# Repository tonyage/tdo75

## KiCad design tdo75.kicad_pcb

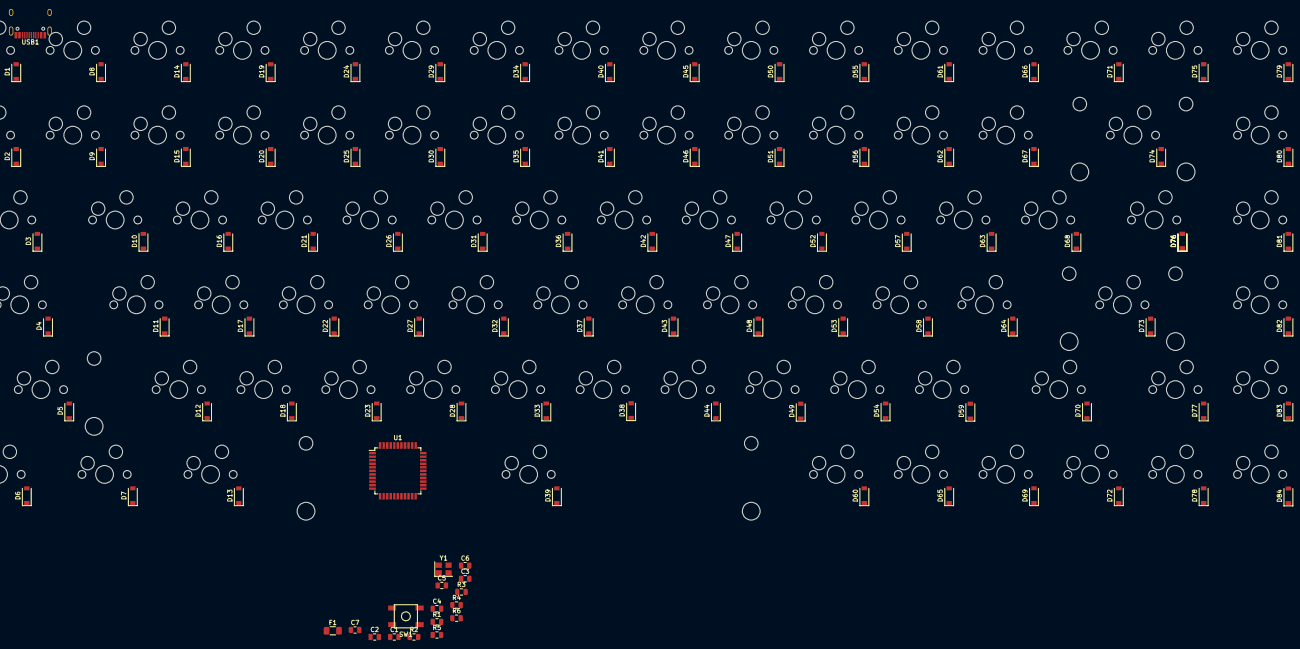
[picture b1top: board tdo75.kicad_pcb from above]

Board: 2 copper layers, 187 parts (0 on the bottom side), 120 nets, no tracks yet.

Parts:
C1, C3, C4: 0.1uF; C_0805_2012Metric
C2: 1uF; C_0805_2012Metric
C5, C6: 22pF; C_0805_2012Metric
C7: 10uF; C_0805_2012Metric
D1, D2, D3, D4, D5, D6, D7, D8, D9, D10, D11, D12, D13, D14, D15, D16, D17, D18, D19, D20, D21, D22, D23, D24, D25, D26, D27, D28, D29, D30, D31, D32, D33, D34, D35, D36, D37, D38, D39, D40, D41, D42, D43, D44, D45, D46, D47, D48, D49, D50, D51, D52, D53, D54, D55, D56, D57, D58, D59, D60, D61, D62, D63, D64, D65, D66, D67, D68, D69, D70, D71, D72, D73, D74, D75, D76, D76#2, D77, D78, D79, D80, D81, D82, D83, D84: D_Small; D_SOD-123
F1: 500mA; Fuse_1206_3216Metric
MX1, MX2, MX8, MX9, MX10, MX11, MX12, MX14, MX15, MX16, MX17, MX18, MX19, MX20, MX21, MX22, MX23, MX24, MX25, MX26, MX27, MX28, MX29, MX30, MX31, MX32, MX33, MX34, MX35, MX36, MX37, MX38, MX40, MX41, MX42, MX43, MX44, MX45, MX46, MX47, MX48, MX49, MX50, MX51, MX52, MX53, MX54, MX55, MX56, MX57, MX58, MX59, MX60, MX61, MX62, MX63, MX64, MX65, MX66, MX67, MX68, MX69, MX71, MX72, MX75, MX77, MX78, MX79, MX80, MX81, MX82, MX83, MX84: MX-NoLED; MXOnly-1U-Hotswap
MX3, MX76: MX-NoLED; MXOnly-1.5U-Hotswap
MX4, MX70: MX-NoLED; MXOnly-1.75U-Hotswap
MX5, MX73: MX-NoLED; MXOnly-2.25U-Hotswap
MX6, MX7, MX13: MX-NoLED; MXOnly-1.25U-Hotswap
MX39: MX-NoLED; MXOnly-6.25U-Hotswap
MX74: MX-NoLED; MXOnly-2U-Hotswap
R1, R2: 5.1k; R_0805_2012Metric
R3, R4: 22; R_0805_2012Metric
R5, R6: 10k; R_0805_2012Metric
SW1: SW_Push; SKQG-1155865
U1: ATmega32U4-AU; TQFP-44_10x10mm_P0.8mm
USB1: HRO-TYPE-C-31-M-12
Y1: 16MHz; Crystal_SMD_3225-4Pin_3.2x2.5mm

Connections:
+5V: C1.1, C3.1, C4.1, C7.1, F1.1, R5.2, U1.2, U1.7, U1.14, U1.24, U1.34, U1.44
COL0: MX1.1, MX2.1, MX3.1, MX4.1, MX5.1, MX6.1, U1.8
COL1: MX7.1, MX8.1, MX9.1, MX10.1, MX11.1, MX12.1, U1.9
COL2: MX13.1, MX14.1, MX15.1, MX16.1, MX17.1, MX18.1, U1.10
COL3: MX19.1, MX20.1, MX21.1, MX22.1, MX23.1, U1.11
COL4: MX24.1, MX25.1, MX26.1, MX27.1, MX28.1, U1.28
COL5: MX29.1, MX30.1, MX31.1, MX32.1, MX33.1, U1.29
COL6: MX34.1, MX35.1, MX36.1, MX37.1, MX38.1, MX39.1, U1.30
COL7: MX40.1, MX41.1, MX42.1, MX43.1, MX44.1, U1.12
COL8: MX45.1, MX46.1, MX47.1, MX48.1, MX49.1, U1.18
COL9: MX50.1, MX51.1, MX52.1, MX53.1, MX54.1, U1.19
COL10: MX55.1, MX56.1, MX57.1, MX58.1, MX59.1, MX60.1, U1.20
COL11: MX61.1, MX62.1, MX63.1, MX64.1, MX65.1, U1.21
COL12: MX66.1, MX67.1, MX68.1, MX69.1, U1.25
COL13: MX70.1, MX71.1, MX72.1, U1.22
COL14: MX73.1, MX74.1, MX75.1, MX76.1, MX77.1, MX78.1, U1.26
COL15: MX79.1, MX80.1, MX81.1, MX82.1, MX83.1, MX84.1, U1.27
D+: R4.2, USB1.6, USB1.8
D-: R3.2, USB1.5, USB1.7
GND: C1.2, C2.2, C3.2, C4.2, C5.2, C6.2, C7.2, R1.1, R2.1, R6.1, SW1.1, U1.5, U1.15, U1.23, U1.35, U1.43, USB1.1, USB1.12, USB1.13, Y1.2, Y1.4
unnamed: C2.1, U1.6
unnamed: C5.1, U1.17, Y1.1
unnamed: C6.1, U1.16, Y1.3
unnamed: D1.2, MX1.2
unnamed: D2.2, MX2.2
unnamed: D3.2, MX3.2
unnamed: D4.2, MX4.2
unnamed: D5.2, MX5.2
unnamed: D6.2, MX6.2
unnamed: D7.2, MX7.2
unnamed: D8.2, MX8.2
unnamed: D9.2, MX9.2
unnamed: D10.2, MX10.2
unnamed: D4.1, D11.1, D17.1, D22.1, D27.1, D32.1, D37.1, D43.1, D48.1, D53.1, D58.1, D64.1, D73.1, D82.1
unnamed: D11.2, MX11.2
unnamed: D12.2, MX12.2
unnamed: D13.2, MX13.2
unnamed: D14.2, MX14.2
unnamed: D15.2, MX15.2
unnamed: D16.2, MX16.2
unnamed: D17.2, MX17.2
unnamed: D18.2, MX18.2
unnamed: D19.2, MX19.2
unnamed: D20.2, MX20.2
unnamed: D21.2, MX21.2
unnamed: D22.2, MX22.2
unnamed: D23.2, MX23.2
unnamed: D24.2, MX24.2
unnamed: D25.2, MX25.2
unnamed: D26.2, MX26.2
unnamed: D27.2, MX27.2
unnamed: D28.2, MX28.2
unnamed: D29.2, MX29.2
unnamed: D30.2, MX30.2
unnamed: D31.2, MX31.2
unnamed: D32.2, MX32.2
unnamed: D33.2, MX33.2
unnamed: D34.2, MX34.2
unnamed: D35.2, MX35.2
unnamed: D36.2, MX36.2
unnamed: D37.2, MX37.2
unnamed: D38.2, MX38.2
unnamed: D39.2, MX39.2
unnamed: D40.2, MX40.2
unnamed: D41.2, MX41.2
unnamed: D42.2, MX42.2
unnamed: D43.2, MX43.2
unnamed: D44.2, MX44.2
unnamed: D45.2, MX45.2
unnamed: D46.2, MX46.2
unnamed: D47.2, MX47.2
unnamed: D48.2, MX48.2
unnamed: D49.2, MX49.2
unnamed: D50.2, MX50.2
unnamed: D51.2, MX51.2
unnamed: D52.2, MX52.2
unnamed: D53.2, MX53.2
unnamed: D54.2, MX54.2
unnamed: D55.2, MX55.2
unnamed: D56.2, MX56.2
unnamed: D57.2, MX57.2
unnamed: D58.2, MX58.2
unnamed: D59.2, MX59.2
unnamed: D60.2, MX60.2
unnamed: D61.2, MX61.2
unnamed: D62.2, MX62.2
unnamed: D63.2, MX63.2
unnamed: D64.2, MX64.2
unnamed: D65.2, MX65.2
unnamed: D66.2, MX66.2
unnamed: D67.2, MX67.2
unnamed: D68.2, MX68.2
unnamed: D69.2, MX69.2
unnamed: D70.2, MX70.2
unnamed: D71.2, MX71.2
unnamed: D72.2, MX72.2
unnamed: D73.2, MX73.2
unnamed: D74.2, MX74.2
unnamed: D75.2, MX75.2
unnamed: D76.2, D76#2.2, MX76.2
unnamed: D77.2, MX77.2
unnamed: D78.2, MX78.2
unnamed: D79.2, MX79.2
unnamed: D80.2, MX80.2
unnamed: D81.2, MX81.2
unnamed: D82.2, MX82.2
unnamed: D83.2, MX83.2
unnamed: D84.2, MX84.2
unnamed: R1.2, USB1.10
unnamed: R2.2, USB1.4
unnamed: R3.1, U1.3
unnamed: R4.1, U1.4
unnamed: R5.1, SW1.2, U1.13
unnamed: R6.2, U1.33
ROW0: D1.1, D8.1, D14.1, D19.1, D24.1, D29.1, D34.1, D40.1, D45.1, D50.1, D55.1, D61.1, D66.1, D71.1, D75.1, D79.1, U1.41
ROW1: D2.1, D9.1, D15.1, D20.1, D25.1, D30.1, D35.1, D41.1, D46.1, D51.1, D56.1, D62.1, D67.1, D74.1, D80.1, U1.40
ROW2: D3.1, D10.1, D16.1, D21.1, D26.1, D31.1, D36.1, D42.1, D47.1, D52.1, D57.1, D63.1, D68.1, D76.1, D76#2.1, D81.1, U1.39
ROW4: D5.1, D12.1, D18.1, D23.1, D28.1, D33.1, D38.1, D44.1, D49.1, D54.1, D59.1, D70.1, D77.1, D83.1, U1.37
ROW5: D6.1, D7.1, D13.1, D39.1, D60.1, D65.1, D69.1, D72.1, D78.1, D84.1
VCC: F1.2, USB1.2, USB1.11

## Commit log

2020-03-17 Initial commit, KiCad generatated files
2020-03-17 Adding KiCad libraries for switches and connectors
2020-03-17 Adding KiCad gitignore and generated symbole and footprint lib tables
2020-03-19 type-c first pass
2020-03-22 map footprints to schematics
2020-03-22 heirarchical keyboard matrix
2020-03-22 initial 75% switch layout, walking back stepped capslock :(
